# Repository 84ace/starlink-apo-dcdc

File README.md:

<h1 align="center">

  Ace's Electronics Pty Ltd  
  DC-DC converter for use in 12/24 volt systems
</h1>

# Looking to get up and running?
- [Wiki - Quickstart Guide](../../wiki/Quickstart-Guide)

# Project Goals:
The overall goal of this project is to make a simple, robust and reliable DC-DC converter for use in cars with smart alternators, such as the Next Gen Ranger and Everest. The DC-DC converter will be solid state and be able to handle input voltages in the range of 9-32V and output 25V 2.5A, or 62.5W.

# Design goals:  
- Smallest form-factor possible while being able to handle ~60W without getting too hot
- Can be used in-line with any cheap pass-through Starlink auxiliary 12V adapter
- Zero configuration
- Zero maintenance

# v0.0.1
Version 0.0.1 has been prototyped. I will hand assemble some test boards and do some testing. ~ETA for completion is 10/8/25.

# Where to Buy:
TBA, but most likely will be vvailable to purchase in Australia or New Zealand via <a href="https://d1b959-f7.myshopify.com/">The AE Store</a>

## Support:
Contact me direct via ace<@>aceselectronics.com.au, just make it look like a normal email address. (hiding from the bots ;)

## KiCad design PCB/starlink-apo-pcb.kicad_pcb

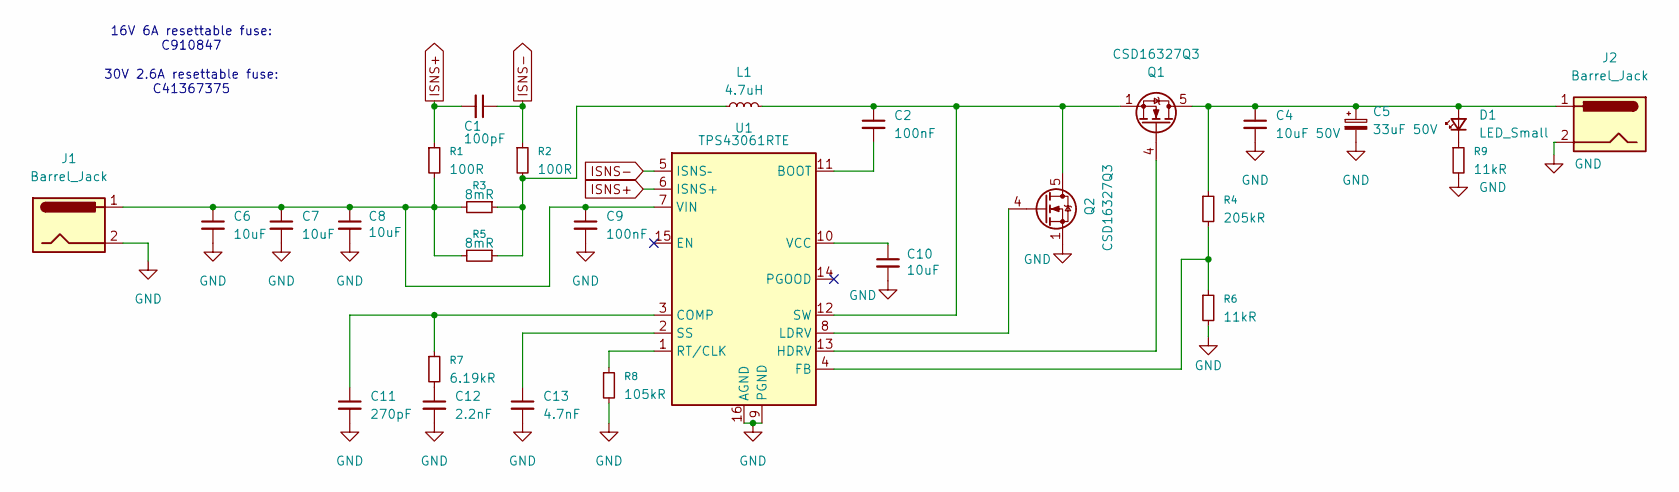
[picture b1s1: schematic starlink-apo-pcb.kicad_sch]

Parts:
C1: 100pF; C_0603_1608Metric; lcsc C14858
C2, C9: 100nF; C_0603_1608Metric; lcsc C14663
C4: 10uF 50V; C_1210_3225Metric; lcsc C138687
C5: 33uF 50V; C_Elec_6.3x7.7; lcsc C402500
C6, C7, C8: 10uF; C_1210_3225Metric; lcsc C138687
C10: 10uF; C_0603_1608Metric; lcsc C96446
C11: 270pF; C_0603_1608Metric; lcsc C1608
C12: 2.2nF; C_0603_1608Metric; lcsc C107082
C13: 4.7nF; C_0603_1608Metric; lcsc C597215
D1: LED_Small; LED_0402_1005Metric; lcsc C779449
J1, J2: Barrel_Jack; BarrelJack_Wuerth_6941xx301002; lcsc C3096082
L1: 4.7uH; L_Coilcraft_XAL7030-472; lcsc C19191671
Q1, Q2: CSD16327Q3; VSON-8_3.3x3.3mm_P0.65mm_NexFET; lcsc C840100
R1, R2: 100R; R_0603_1608Metric; lcsc C105588
R3, R5: 8mR; R_1206_3216Metric; lcsc C1021507
R4: 205kR; R_0603_1608Metric; lcsc C861745
R6, R9: 11kR; R_0603_1608Metric; lcsc C473242
R7: 6.19kR; R_0603_1608Metric; lcsc C228022
R8: 105kR; R_0603_1608Metric; lcsc C2933128
U1: TPS43061RTE; WQFN-16-1EP_3x3mm_P0.5mm_EP1.6x1.6mm_ThermalVias; lcsc C527683

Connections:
GND: C4.2, C5.2, C6.2, C7.2, C8.2, C9.2, C10.2, C11.2, C12.2, C13.2, J1.2, J2.2, Q2.1 (S), Q2.2 (S), Q2.3 (S), R6.2, R8.2, R9.2, U1.9 (PGND), U1.16 (AGND), U1.17 (AGND)
ISNS+: C1.2, R1.1, U1.6 (ISNS+)
ISNS-: C1.1, R2.1, U1.5 (ISNS–)
unnamed: C12.1, R7.2
unnamed: C4.1, C5.1, D1.2 (A), J2.1, Q1.5 (D), R4.1
unnamed: D1.1 (K), R9.1
unnamed: L1.1, R2.2, R3.1, R5.1
unnamed: Q1.4 (G), U1.13 (HDRV)
unnamed: C2.1, L1.2, Q1.1 (S), Q1.2 (S), Q1.3 (S), Q2.5 (D), U1.12 (SW)
unnamed: Q2.4 (G), U1.8 (LDRV)
unnamed: C2.2, U1.11 (BOOT)
unnamed: C11.1, R7.1, U1.3 (COMP)
unnamed: R4.2, R6.1, U1.4 (FB)
unnamed: R8.1, U1.1 (RT/CLK)
unnamed: C13.1, U1.2 (SS)
unnamed: C10.1, U1.10 (VCC)
unnamed: C6.1, C7.1, C8.1, C9.1, J1.1, R1.2, R3.2, R5.2, U1.7 (VIN)

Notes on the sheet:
16V 6A resettable fuse: C910847 30V 2.6A resettable fuse: C41367375

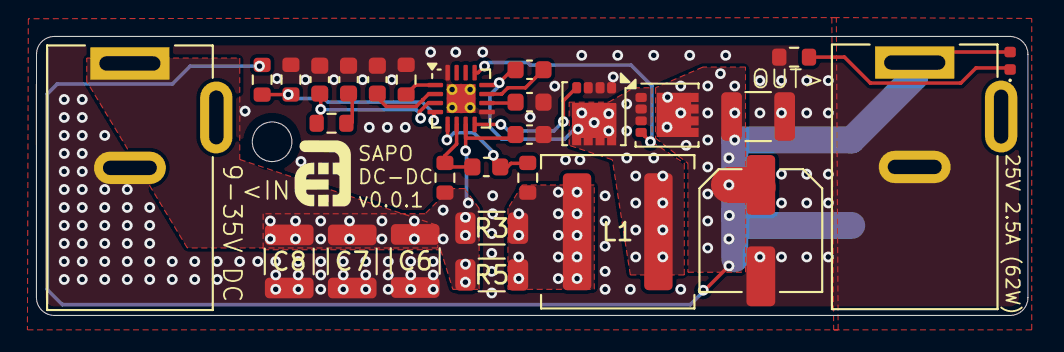
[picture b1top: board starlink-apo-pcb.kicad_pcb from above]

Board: 2 copper layers, 55.1 x 15.5 mm, 28 parts (0 on the bottom side), 17 nets.

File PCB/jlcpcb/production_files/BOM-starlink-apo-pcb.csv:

Comment,Designator,Footprint,LCSC,Quantity
8mR,"R3,R5",R_1206_3216Metric,C1021507,2
10uF 50V,"C4,C6,C7,C8",C_1210_3225Metric,C138687,4
100nF,"C2,C9",C_0603_1608Metric,C14663,2
100pF,C1,C_0603_1608Metric,C14858,1
2.2nF,C12,C_0603_1608Metric,C1604,1
270pF,C11,C_0603_1608Metric,C1608,1
4.7uH,L1,L_Coilcraft_XAL7030-472,C19191671,1
100R,"R1,R2",R_0603_1608Metric,C22775,2
6.19kR,R7,R_0603_1608Metric,C228022,1
11kR,"R6,R9",R_0603_1608Metric,C25950,2
105kR,R8,R_0603_1608Metric,C2933128,1
Barrel_Jack,"J1,J2",BarrelJack_Wuerth_6941xx301002,C3096082,2
33uF 50V,C5,C_Elec_6.3x7.7,C402500,1
205kR,R4,R_0603_1608Metric,C5126104,1
TPS43061RTE,U1,WQFN-16-1EP_3x3mm_P0.5mm_EP1.6x1.6mm_ThermalVias,C527683,1
4.7nF,C13,C_0603_1608Metric,C53987,1
LED_Small,D1,LED_0402_1005Metric,C779449,1
CSD16327Q3,"Q1,Q2",VSON-8_3.3x3.3mm_P0.65mm_NexFET,C840100,2
10uF,C10,C_0603_1608Metric,C96446,1

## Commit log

2025-07-18 setting up repo
2025-07-19 v0.0.1 off to JLCPCB
